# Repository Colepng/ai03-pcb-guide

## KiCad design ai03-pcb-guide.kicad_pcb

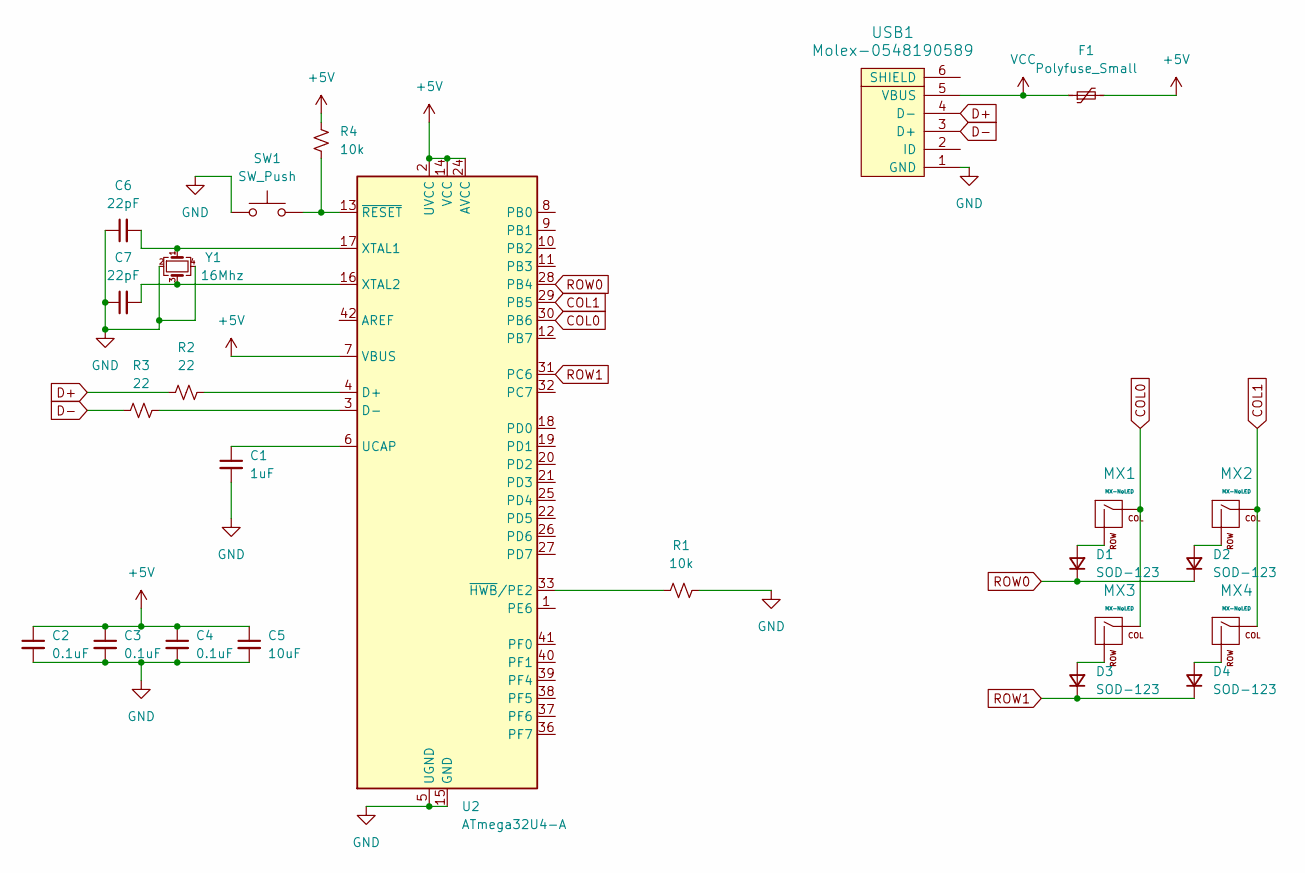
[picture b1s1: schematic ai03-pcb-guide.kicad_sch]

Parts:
C1: 1uF; C_0805_2012Metric_Pad1.18x1.45mm_HandSolder
C2, C3, C4: 0.1uF; C_0805_2012Metric_Pad1.18x1.45mm_HandSolder
C5: 10uF; C_0805_2012Metric_Pad1.18x1.45mm_HandSolder
C6, C7: 22pF; C_0805_2012Metric_Pad1.18x1.45mm_HandSolder
D1: SOD-123; D_SOD-128
D2, D3, D4: SOD-123; D_SOD-123
F1: Polyfuse_Small; Fuse_1206_3216Metric_Pad1.42x1.75mm_HandSolder
MX1, MX2, MX3, MX4: MX-NoLED; MX-1U-NoLED
R1, R4: 10k; R_0805_2012Metric_Pad1.20x1.40mm_HandSolder
R2, R3: 22; R_0805_2012Metric_Pad1.20x1.40mm_HandSolder
SW1: SW_Push; SKQG-1155865
U2: ATmega32U4-A; TQFP-44_10x10mm_P0.8mm
USB1: Molex-0548190589
Y1: 16Mhz; Crystal_SMD_3225-4Pin_3.2x2.5mm_HandSoldering

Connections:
+5V: C2.1, C3.1, C4.1, C5.1, F1.2, R4.1, U2.2 (UVCC), U2.7 (VBUS), U2.14 (VCC), U2.24 (AVCC), U2.34 (VCC), U2.44 (AVCC)
COL0: MX1.1 (COL), MX3.1 (COL), U2.30 (PB6)
COL1: MX2.1 (COL), MX4.1 (COL), U2.29 (PB5)
D+: R2.1, USB1.4 (D-)
D-: R3.1, USB1.3 (D+)
GND: C1.2, C2.2, C3.2, C4.2, C5.2, C6.1, C7.1, R1.2, SW1.1, U2.5 (UGND), U2.15 (GND), U2.23 (GND), U2.35 (GND), U2.43 (GND), USB1.1 (GND), Y1.2, Y1.4
unnamed: D1.2 (A), MX1.2 (ROW)
unnamed: D2.2 (A), MX2.2 (ROW)
unnamed: D3.2 (A), MX3.2 (ROW)
unnamed: D4.2 (A), MX4.2 (ROW)
unnamed: R2.2, U2.4 (D+)
unnamed: R3.2, U2.3 (D-)
unnamed: C1.1, U2.6 (UCAP)
unnamed: C6.2, U2.17 (XTAL1), Y1.1
unnamed: C7.2, U2.16 (XTAL2), Y1.3
unnamed: R1.1, U2.33 (~HWB/PE2)
unnamed: R4.2, SW1.2, U2.13 (~RESET)
ROW0: D1.1 (K), D2.1 (K), U2.28 (PB4)
ROW1: D3.1 (K), D4.1 (K), U2.31 (PC6)
VCC: F1.1, USB1.5 (VBUS)

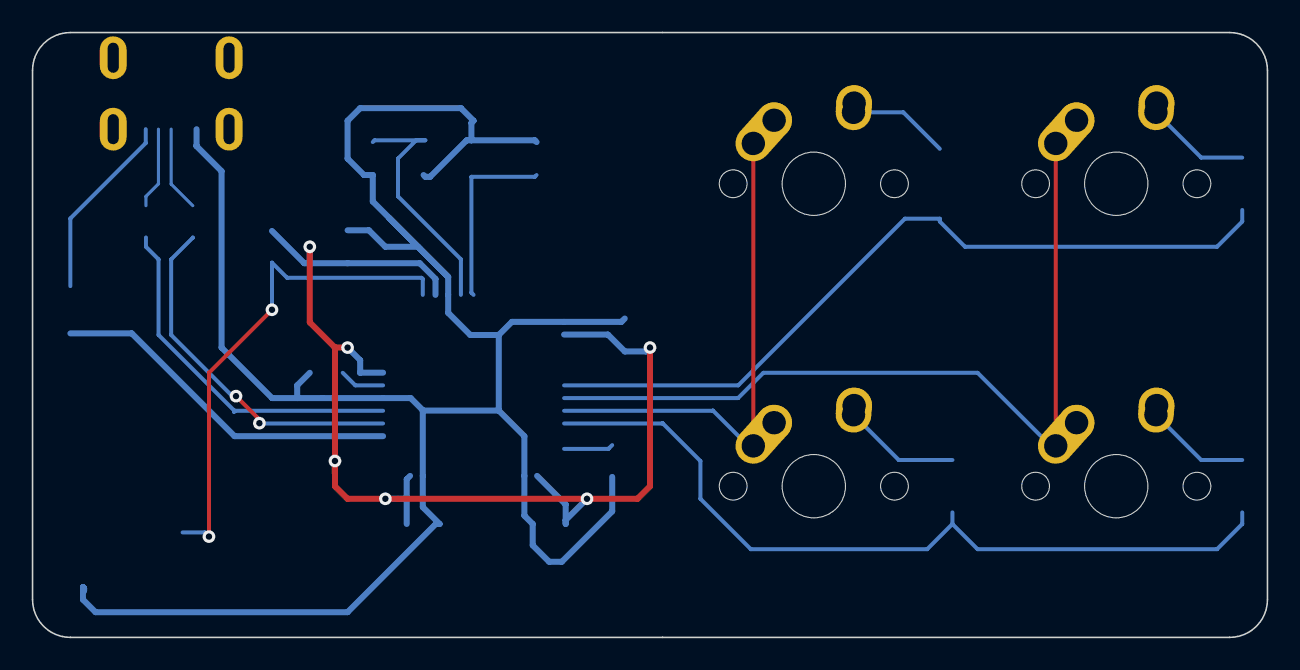
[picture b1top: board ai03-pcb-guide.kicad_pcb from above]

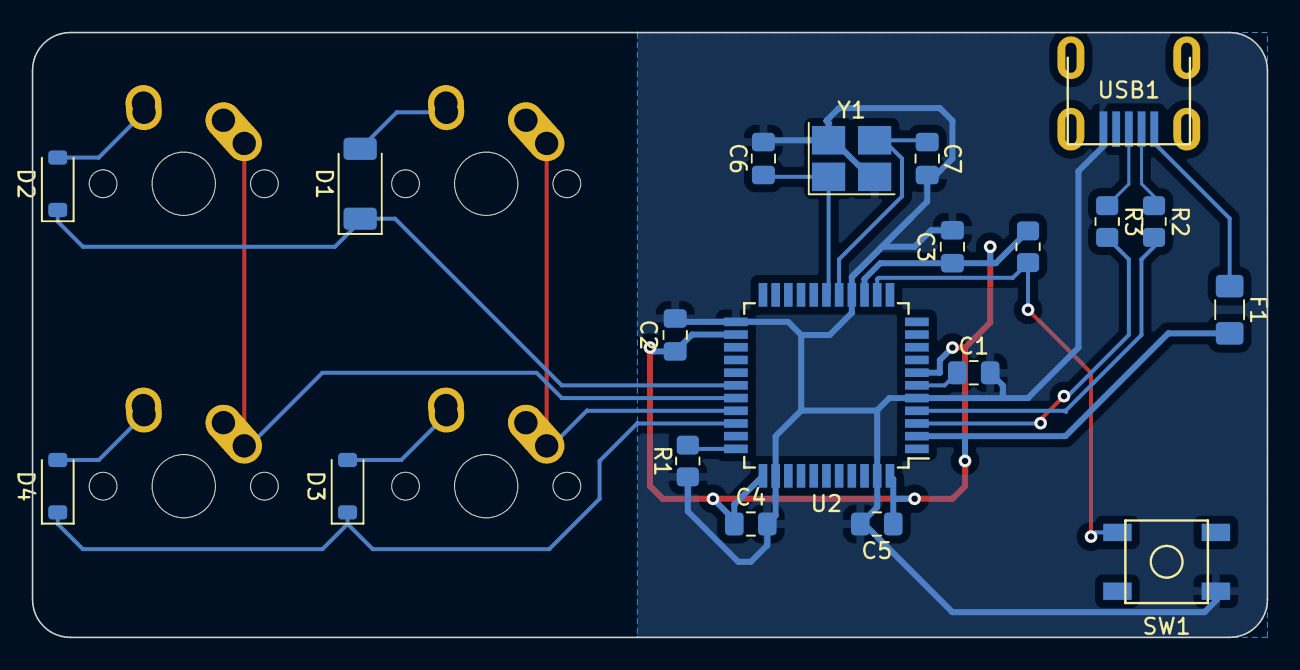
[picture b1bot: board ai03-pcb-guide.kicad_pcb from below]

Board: 2 copper layers, 77.8 x 38.1 mm, 24 parts (20 on the bottom side), 20 nets.

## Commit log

2023-05-18 Init kicad project
2023-05-18 Add kicad libs as git submodels
2023-05-18 Add libs to footprints and symbols
2023-05-18 Finished mcu schematic
2023-05-18 Add usb to schematic
2023-05-18 Finish matrix and assign footprints
2023-05-18 Done routing
2023-05-18 Done the guide
